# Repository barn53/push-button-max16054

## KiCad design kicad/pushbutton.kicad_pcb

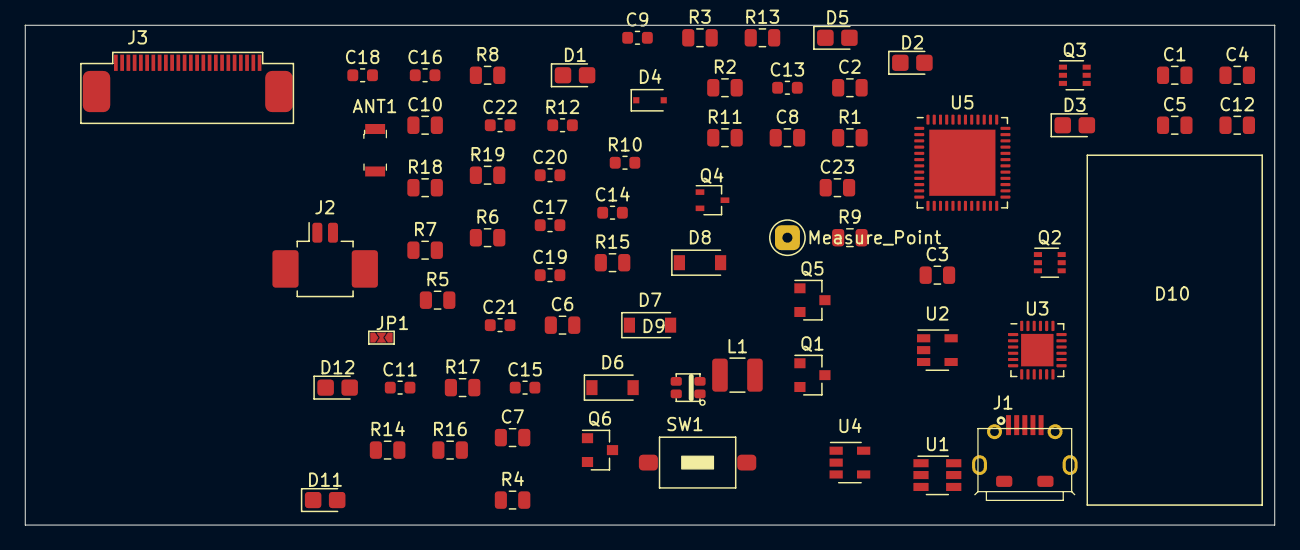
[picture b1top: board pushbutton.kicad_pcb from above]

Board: 2 copper layers, 100.0 x 40.0 mm, 73 parts (0 on the bottom side), 48 nets, no tracks yet.

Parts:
ANT1: 2450AT18A100E; Antenna_1.6x3.2mm_2450AT18A100E
C1, C12, C23: 100n; C_0805_2012Metric
C2, C6, C8, C10: 1u; C_0805_2012Metric
C3, C4, C5, C7: 4.7u; C_0805_2012Metric
C9: 4.7u; C_0603_1608Metric
C11, C13: 100n; C_0603_1608Metric
C14, C15, C16, C17, C18, C19, C20, C21, C22: 1u; C_0603_1608Metric
D1: charge; LED_0805_2012Metric_Castellated
D2: ready; LED_0805_2012Metric_Castellated
D3: TxD; LED_0805_2012Metric_Castellated
D4: NSR0320; D_SOD-323F
D5: RxD; LED_0805_2012Metric_Castellated
D6, D7, D8: MBR0530; D_SOD-123
D9: WS2812B-2020
D10: IPSDisplay_80x160; IPS_Display_80x160_Bottom_1.6mm
D11: LED Red; LED_0805_2012Metric_Castellated
D12: LED Blue; LED_0805_2012Metric_Castellated
J1: USB_B_Micro; MicroUSB_through_hole_fixing
J2: Conn_01x02_Male; Molex_PicoBlade_53261-0271_1x02-1MP_P1.25mm_Horizontal
J3: Conn_01x24; FPC_24_JUSHUO-AFC07-S24ECA
JP1: SolderJumper_3_Open; SolderJumper-3_small
L1: 68uH; L_1210_3225Metric
M1: Measure_Point; Measure_Point_Through
Q1: SI2301; SOT-23
Q2, Q3: PMBT2222AYS; SOT-363_SC-70-6
Q4: Si1308EDL; SOT-323_SC-70
Q5: IRLML6402; SOT-23
Q6: S8050_J3Y; SOT-23
R1: 2k; R_0805_2012Metric
R2, R3: 470; R_0805_2012Metric
R4, R7, R8, R11, R13, R15, R16: 10k; R_0805_2012Metric
R5, R6: 180; R_0805_2012Metric
R9: 100k; R_0805_2012Metric
R10: 10k; R_0603_1608Metric
R12: 0.47; R_0603_1608Metric
R14: 1k; R_0805_2012Metric
R17: 10; R_0805_2012Metric
R18, R19: ?; R_0805_2012Metric
SW1: SW_Push; SMD_Push_Button
U1: MAX16054; TSOT-23-6
U2: MCP73831-2-OT; SOT-23-5
U3: CP2104; QFN-24-1EP_4x4mm_P0.5mm_EP2.6x2.6mm
U4: TLV75533PDBV; SOT-23-5
U5: ESP32-PICO-D4; QFN-48-1EP_7x7mm_P0.5mm_EP5.3x5.3mm

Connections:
+3V3: C8.1, C9.2, C13.1, C23.1, D10.10, D10.12, J3.15, J3.16, JP1.3, L1.2, R11.2, R13.2, R16.1, U4.5
/ADC: R18.2, R19.1
/D+: J1.3, U3.3
/D-: J1.2, U3.4
/DTR: Q3.1, R7.2, U3.23
/EPD_BS: J3.8, JP1.2
/EPD_GDR: J3.2, Q4.1, R10.1
/EPD_PREVGH: C19.1, D8.1, J3.21
/EPD_PREVGL: C21.1, D7.2, J3.23
/EPD_RESE: J3.3, Q4.2, R12.1
/EPD_VCOM: C22.1, J3.24
/EPD_VDD: C16.1, J3.18
/EPD_VGH: C15.1, J3.5
/EPD_VGL: C14.1, J3.4
/EPD_VPP: C17.1, J3.19
/EPD_VSH: C18.1, J3.20
/EPD_VSL: C20.1, J3.22
/Flash: Q3.6, R13.1
/GPIO.0: R5.2, U3.14
/GPIO.1: R6.2, U3.13
/LDO_EN: U1.5, U4.3
/LEDK: D10.11, R17.2
/RTS: Q2.1, R8.2, U3.19
/VBat: C7.1, Q1.3, U2.3
/VBus: C2.1, C3.1, D4.2, J1.1, Q1.1, R2.1, R9.1, U2.4, U3.7, U3.8
/VDD: C1.1, C4.1, D3.2, D5.2, R4.1, U3.5, U3.6
/VSupp: C6.1, C10.1, D4.1, Q1.2, Q5.2, R15.1, U1.6, U4.1
/VSwitched: Q5.3, R18.1
/~RESET: C12.1, Q2.6, R11.1
/~Switch: Q5.1, R15.2
GND: C1.2, C2.2, C3.2, C4.2, C5.2, C6.2, C7.2, C8.2, C9.1, C10.2, C12.2, C13.2, C14.2, C15.2, C16.2, C17.2, C18.2, C19.2, C20.2, C21.2, C22.2, C23.2, D6.1, D10.7, D10.8, D10.13, J1.5, J1.6, J3.17, JP1.1, Q6.2, R1.2, R3.2, R9.2, R10.2, R12.2, R19.2, SW1.1, U1.2, U1.3, U2.2, U3.2, U3.25, U4.2
unnamed: C5.1, U3.16
unnamed: C11.1, D8.2, L1.1, Q4.3
unnamed: C11.2, D6.2, D7.1
unnamed: D1.1, D2.2, U2.1
unnamed: D1.2, R2.2
unnamed: D2.1, R3.1
unnamed: D3.1, R5.1
unnamed: D5.1, R6.1
unnamed: Q2.2, R7.1
unnamed: Q3.2, R8.1
unnamed: Q6.1, R14.2, R16.2
unnamed: Q6.3, R17.1
unnamed: R1.1, U2.5
unnamed: R4.2, U3.9
unnamed: SW1.2, U1.1
unnamed: U5.1, U5.43, U5.46
unnamed: U5.3, U5.4

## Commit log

2021-03-03 Initial
2021-04-11 Extended schematics
2021-04-27 updated schematics
